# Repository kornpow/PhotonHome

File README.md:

# PhotonHome
Outlet controller using the Particle Photon eco-system.

This device integrates an outlet controller with a simple external interface to the Photon ecosystem. This allows the many new Photon compatible devices and sensors that are coming out right now to interface with AC power outlets.

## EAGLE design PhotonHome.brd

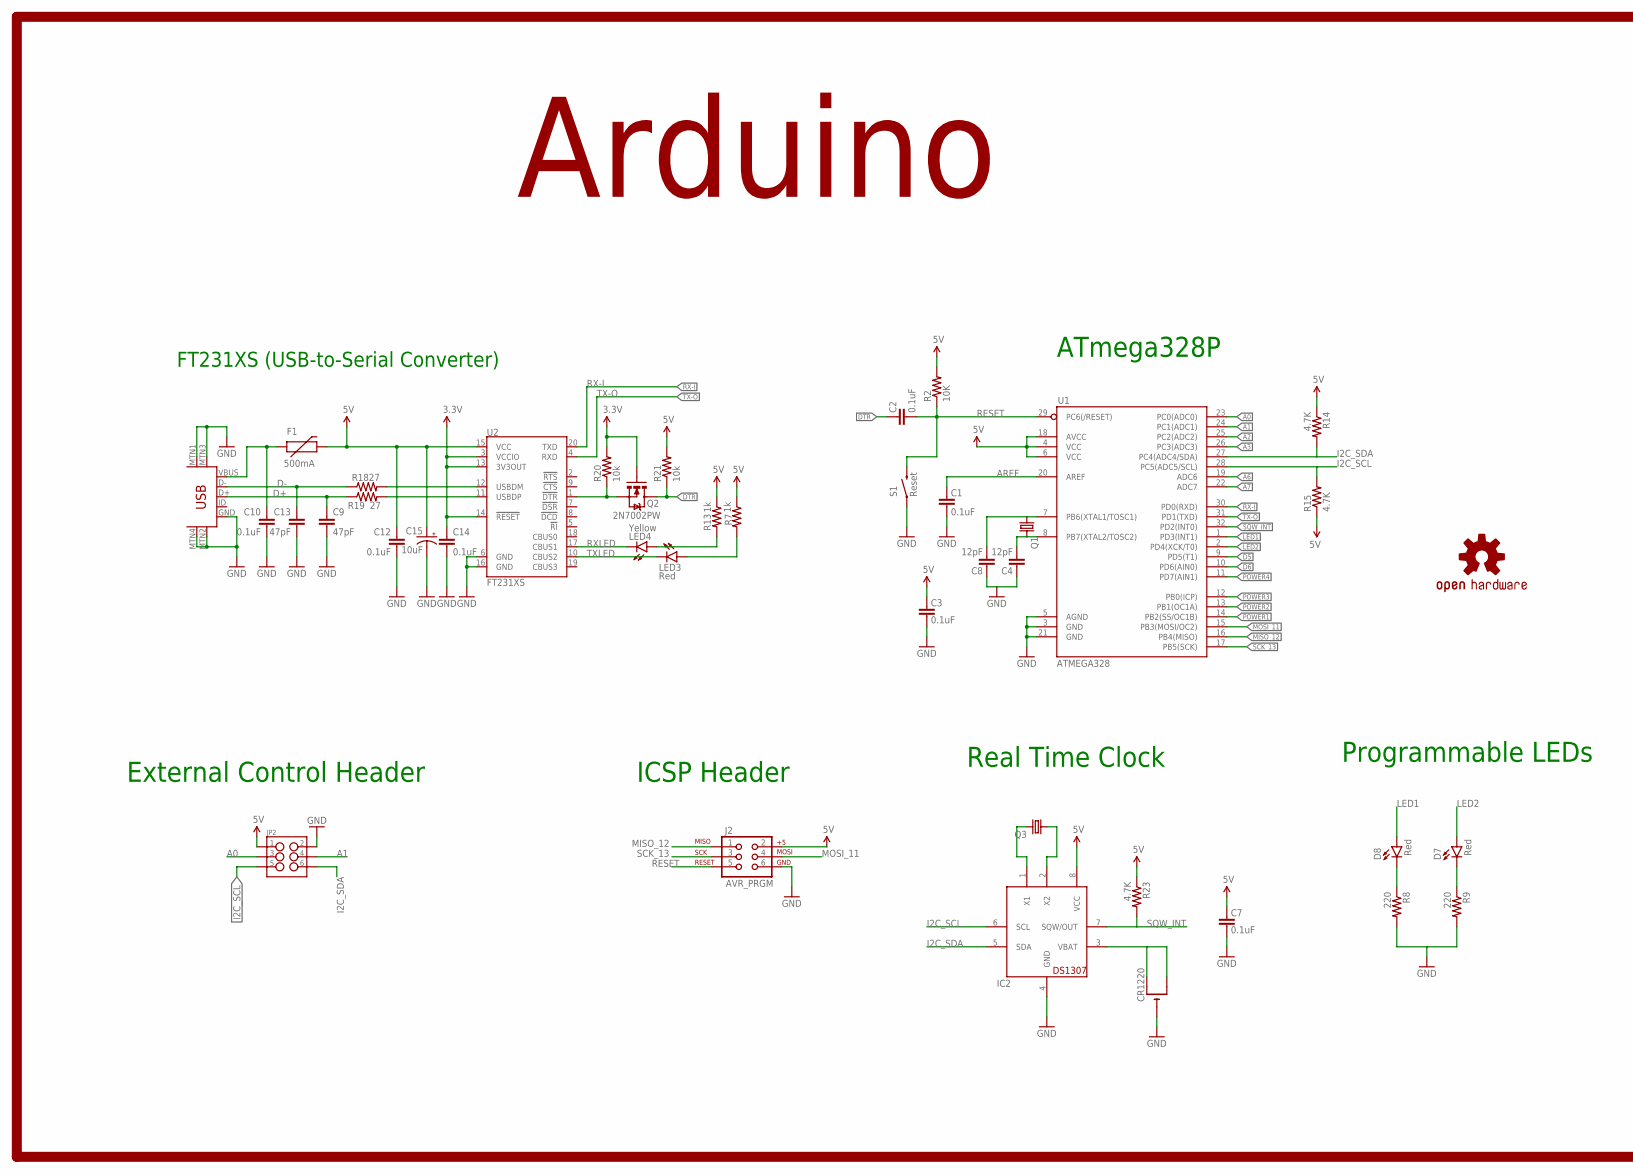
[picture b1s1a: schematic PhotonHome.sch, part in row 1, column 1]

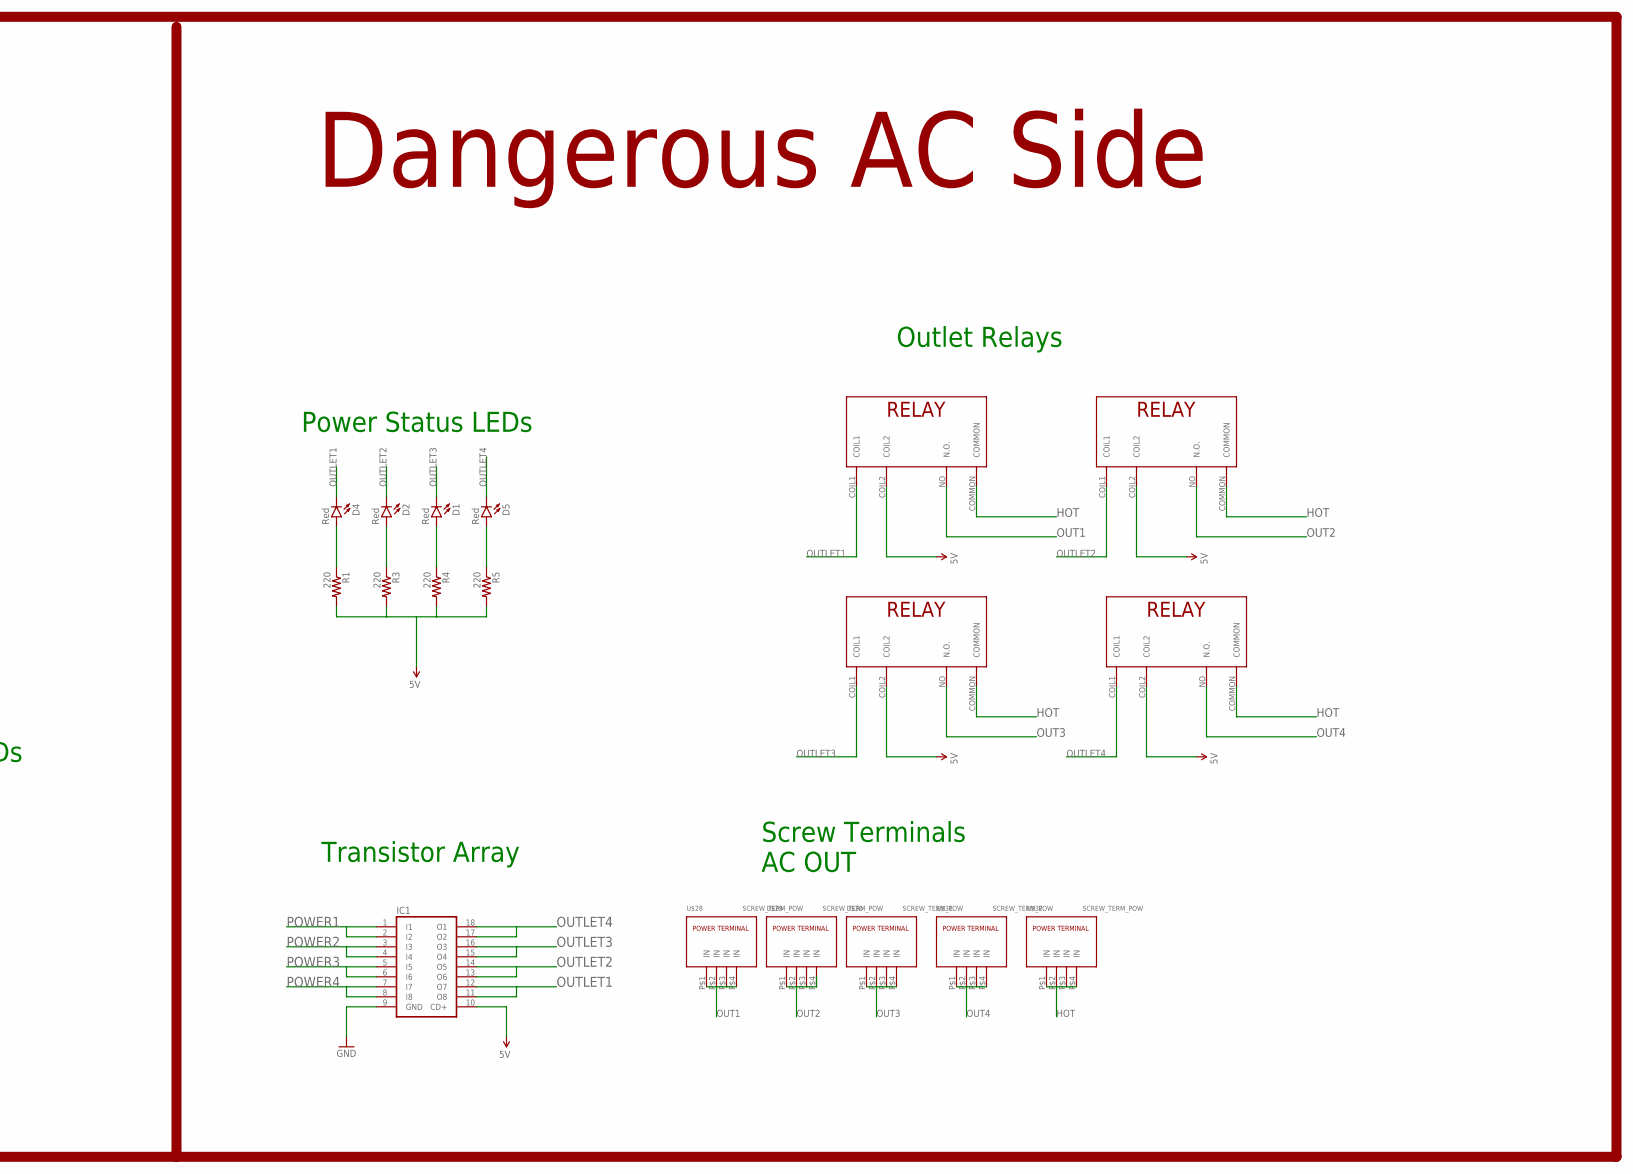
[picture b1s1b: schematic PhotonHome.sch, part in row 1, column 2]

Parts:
C1, C2, C3, C7, C10, C12, C14: 0.1uF; 0805-CAP
C4, C8: 12pF; 0805-CAP
C9, C13: 47pF; 0805-CAP
C15: 10uF; EIA3216
CR1220: CR1220THM; CR1220-THM
D1, D2, D4, D5, D7, D8: Red; 0805-LED
F1: 500mA; PTC-1206
IC1: ULN2803ASOIC18-W; SOIC18-W
IC2: DS1307SO08; SO08-150MIL
J2: AVR_PRGM; 2X3
JP2: M03X2SHROUD; 2X3-SHROUDED
LED3: Red; 0805-LED
LED4: Yellow; 0805-LED
MINIUSB: USB-MINIB-5PIN; USB-MINIB
Q1: CRYSTALHC49UP; HC49UP
Q2: 2N7002PW; SOT323
Q3: CRYSTALTC38H; TC38H
R1, R3, R4, R5, R8, R9: 220; 0805
R2: 10K; 0805
R7, R13: 1k; 0805
R14, R15, R23: 4.7K; 0805
R18, R19: 27; 0805
R20, R21: 10k; 0805
RELAY1, RELAY2, RELAY3, RELAY4: RELAY_NO; RELAY_G2RL-1A
S1: Reset; TACTILE-SWITCH-SMD-ALT01
U1: ATMEGA328; TQFP32-08
U2: FT231XS; SSOP20_L
U$3: OSHW-LOGOS; OSHW-LOGO-S
U$28, U$29, U$30, U$31, U$32: SCREW_TERM_POW; SCREW-TERMINAL-POW

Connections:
3.3V: C14.1, Q2.1 (G), R20.2, U2.3 (VCCIO), U2.13 (3V3OUT), U2.14 (!RESET)
5V: C3.2, C7.2, C12.1, C15.A (+), F1.2, IC1.10 (CD+), IC2.8 (VCC), J2.2, JP2.1, R1.2, R2.2, R3.2, R4.2, R5.2, R7.1, R13.1, R14.1, R15.1, R21.2, R23.1, RELAY1.COIL2, RELAY2.COIL2, RELAY3.COIL2, RELAY4.COIL2, U1.4 (VCC), U1.6 (VCC), U1.18 (AVCC), U2.15 (VCC)
A0: JP2.3, U1.23 (PC0(ADC0))
A1: JP2.4, U1.24 (PC1(ADC1))
A2: U1.25 (PC2(ADC2))
A3: U1.26 (PC3(ADC3))
A6: U1.19 (ADC6)
A7: U1.22 (ADC7)
AREF: C1.2, U1.20 (AREF)
D5: U1.9 (PD5(T1))
D6: U1.10 (PD6(AIN0))
D+: C9.1, MINIUSB.D+, R19.1
D-: C13.1, MINIUSB.D-, R18.1
DTR: C2.2, Q2.3 (D), R21.1
GND: C1.1, C3.1, C4.2, C7.1, C8.2, C9.2, C10.2, C12.2, C13.2, C14.2, C15.C (-), CR1220.-, IC1.9 (GND), IC2.4 (GND), J2.6, JP2.2, MINIUSB.GND, MINIUSB.MTN1 (MTN2), MINIUSB.MTN2 (MTN3), MINIUSB.MTN3 (MTN1), MINIUSB.MTN4, R8.2, R9.2, S1.1, S1.2 (1), U1.3 (GND), U1.5 (AGND), U1.21 (GND), U2.6 (GND), U2.16 (GND)
HOT: RELAY1.COMMON, RELAY2.COMMON, RELAY3.COMMON, RELAY4.COMMON, U$32.P$1, U$32.P$2, U$32.P$3, U$32.P$4
I2C_SCL: IC2.6 (SCL), JP2.5, R15.2, U1.28 (PC5(ADC5/SCL))
I2C_SDA: IC2.5 (SDA), JP2.6, R14.2, U1.27 (PC4(ADC4/SDA))
LED1: D8.1 (A), U1.1 (PD3(INT1))
LED2: D7.1 (A), U1.2 (PD4(XCK/T0))
MISO_12: J2.1, U1.16 (PB4(MISO))
MOSI_11: J2.4, U1.15 (PB3(MOSI/OC2))
unnamed: C4.1, Q1.2, U1.8 (PB7(XTAL2/TOSC2))
unnamed: C8.1, Q1.1, U1.7 (PB6(XTAL1/TOSC1))
unnamed: LED3.1 (A), R7.2
unnamed: D4.1 (A), R1.1
unnamed: D2.1 (A), R3.1
unnamed: D1.1 (A), R4.1
unnamed: D5.1 (A), R5.1
unnamed: D8.2 (C), R8.1
unnamed: LED4.1 (A), R13.2
unnamed: R18.2, U2.12 (USBDM)
unnamed: D7.2 (C), R9.1
unnamed: R19.2, U2.11 (USBDP)
unnamed: Q2.2 (S), R20.1, U2.1 (!DTR)
unnamed: IC2.1 (X1), Q3.2
unnamed: IC2.2 (X2), Q3.1
unnamed: CR1220.+1 (+), CR1220.+2 (+1), IC2.3 (VBAT)
OUT1: RELAY1.NO (N.O.), U$28.P$1, U$28.P$2, U$28.P$3, U$28.P$4
OUT2: RELAY2.NO (N.O.), U$29.P$1, U$29.P$2, U$29.P$3, U$29.P$4
OUT3: RELAY3.NO (N.O.), U$30.P$1, U$30.P$2, U$30.P$3, U$30.P$4
OUT4: RELAY4.NO (N.O.), U$31.P$1, U$31.P$2, U$31.P$3, U$31.P$4
OUTLET1: D4.2 (C), IC1.11 (O8), IC1.12 (O7), RELAY1.COIL1
OUTLET2: D2.2 (C), IC1.13 (O6), IC1.14 (O5), RELAY2.COIL1
OUTLET3: D1.2 (C), IC1.15 (O4), IC1.16 (O3), RELAY3.COIL1
OUTLET4: D5.2 (C), IC1.17 (O2), IC1.18 (O1), RELAY4.COIL1
POWER1: IC1.1 (I1), IC1.2 (I2), U1.14 (PB2(SS/OC1B))
POWER2: IC1.3 (I3), IC1.4 (I4), U1.13 (PB1(OC1A))
POWER3: IC1.5 (I5), IC1.6 (I6), U1.12 (PB0(ICP))
POWER4: IC1.7 (I7), IC1.8 (I8), U1.11 (PD7(AIN1))
RESET: C2.1, J2.5, R2.1, S1.3 (2), S1.4 (2), U1.29 (PC6(/RESET))
RX-I: U1.30 (PD0(RXD)), U2.20 (TXD)
RXLED: LED4.2 (C), U2.17 (CBUS1)
SCK_13: J2.3, U1.17 (PB5(SCK))
SQW_INT: IC2.7 (SQW/OUT), R23.2, U1.32 (PD2(INT0))
TX-O: U1.31 (PD1(TXD)), U2.4 (RXD)
TXLED: LED3.2 (C), U2.10 (CBUS2)
VUSB: C10.1, F1.1, MINIUSB.VBUS

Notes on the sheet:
ICSP Header
ATmega328P
Power Status LEDs
Programmable LEDs
Transistor Array
Real Time Clock
External Control Header
Outlet Relays
Screw Terminals AC OUT
FT231XS (USB-to-Serial Converter)
Arduino
Dangerous AC Side

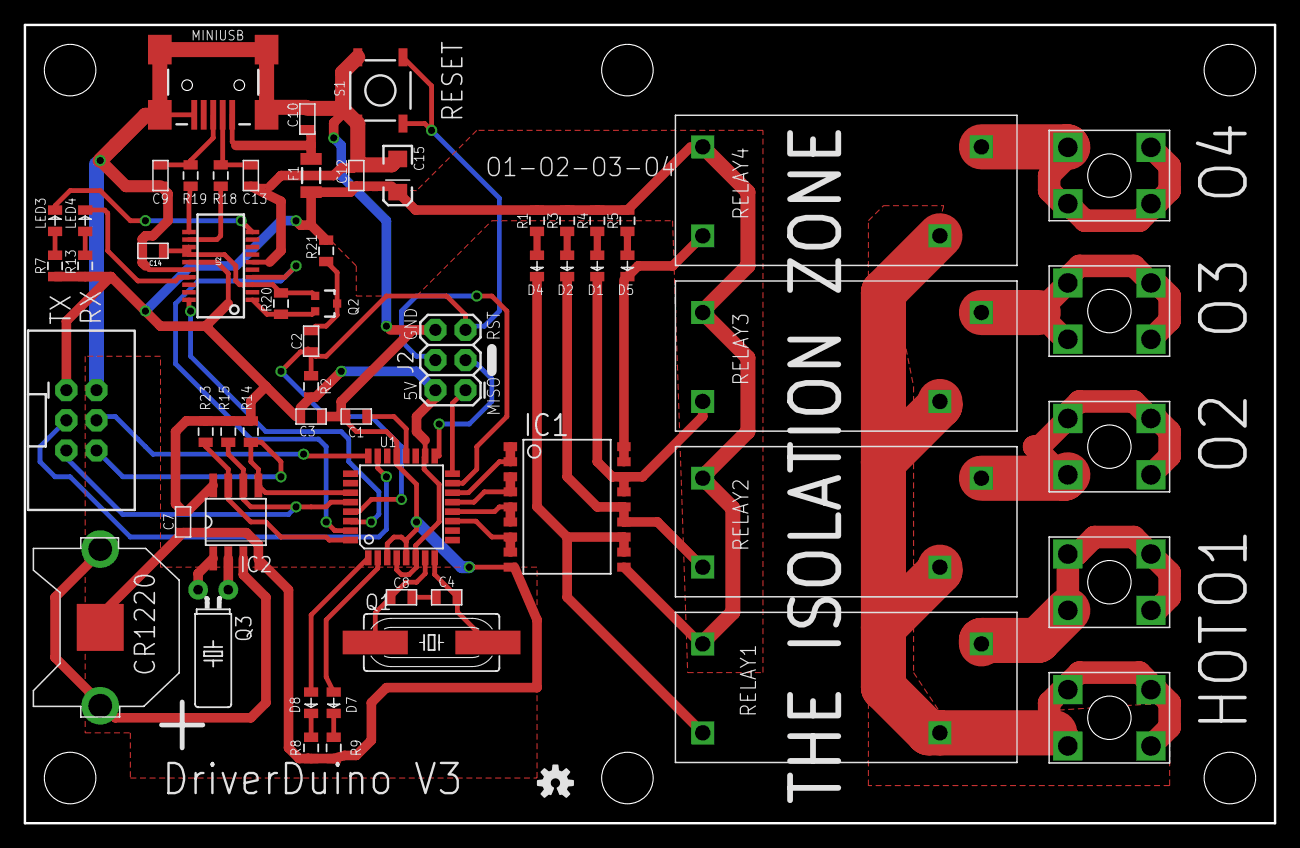
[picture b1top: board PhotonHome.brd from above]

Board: 2 copper layers, 105.4 x 67.3 mm, 60 parts (1 on the bottom side), 52 nets.

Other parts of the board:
U$1: OSHW-LOGOS; OSHW-LOGO-S

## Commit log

2016-01-30 Initial file commit

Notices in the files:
parts and their libraries:
SparkFun-Connectors: Licensing: Creative Commons ShareAlike 4.0 International - https://creativecommons.org/licenses/by-sa/4.0
SparkFun-Capacitors: Licensing: CC v3.0 Share-Alike You are welcome to use this library for commercial purposes.
